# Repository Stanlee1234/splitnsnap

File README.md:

# splitnsnap
A 75% Keyboard, but it is held together in the middle with magnets, making it a regular and split keyboard, whatever you would want.

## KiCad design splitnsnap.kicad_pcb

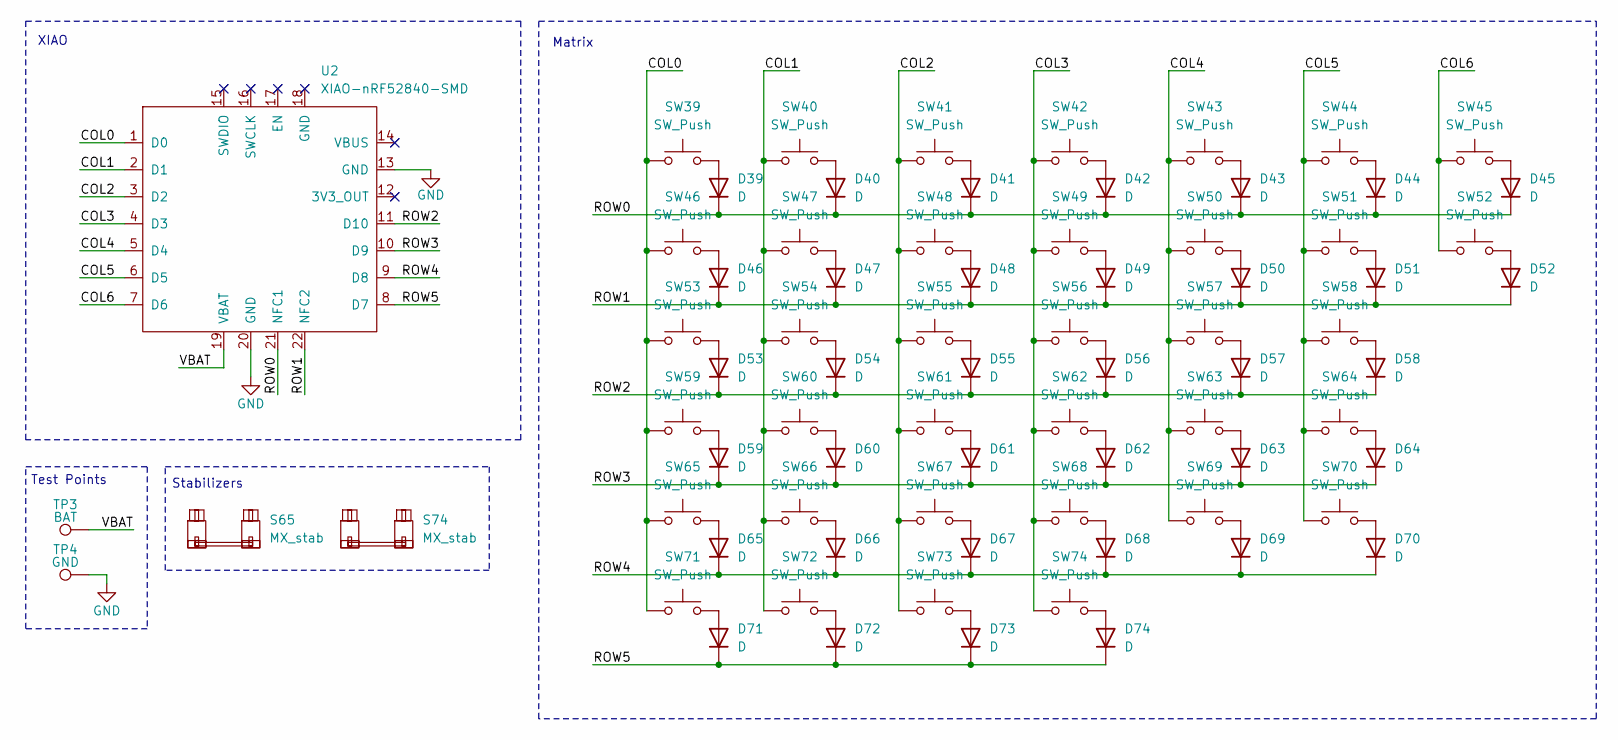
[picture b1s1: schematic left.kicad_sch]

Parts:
D39, D40, D41, D42, D43, D44, D45, D46, D47, D48, D49, D50, D51, D52, D53, D54, D55, D56, D57, D58, D59, D60, D61, D62, D63, D64, D65, D66, D67, D68, D69, D70, D71, D72, D73, D74: D; D_SOD-123
S65: MX_stab; STAB_MX_2.25u
S74: MX_stab; STAB_MX_2.75u
SW39, SW40, SW41, SW42, SW43, SW44, SW45, SW46, SW47, SW48, SW49, SW50, SW51, SW52, SW54, SW55, SW56, SW57, SW58, SW60, SW61, SW62, SW63, SW64, SW66, SW67, SW68, SW69, SW70, SW73: SW_Push; Hotswap_MX_1.00u
SW53: SW_Push; Hotswap_MX_1.50u
SW59: SW_Push; Hotswap_MX_1.75u
SW65: SW_Push; Hotswap_MX_2.25u
SW71, SW72: SW_Push; Hotswap_MX_1.25u
SW74: SW_Push; Hotswap_MX_2.75u
TP3: BAT; TestPoint_Pad_D2.0mm
TP4: GND; TestPoint_Pad_D2.0mm
U2: XIAO-nRF52840-SMD; modified-XIAO-nRF52840-SMD

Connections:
/left/COL0: SW39.1, SW46.1, SW53.1, SW59.1, SW65.1, SW71.1, U2.1 (D0)
/left/COL1: SW40.1, SW47.1, SW54.1, SW60.1, SW66.1, SW72.1, U2.2 (D1)
/left/COL2: SW41.1, SW48.1, SW55.1, SW61.1, SW67.1, SW73.1, U2.3 (D2)
/left/COL3: SW42.1, SW49.1, SW56.1, SW62.1, SW68.1, SW74.1, U2.4 (D3)
/left/COL4: SW43.1, SW50.1, SW57.1, SW63.1, SW69.1, U2.5 (D4)
/left/COL5: SW44.1, SW51.1, SW58.1, SW64.1, SW70.1, U2.6 (D5)
/left/COL6: SW45.1, SW52.1, U2.7 (D6)
/left/ROW0: D39.1 (K), D40.1 (K), D41.1 (K), D42.1 (K), D43.1 (K), D44.1 (K), D45.1 (K), U2.21 (NFC1)
/left/ROW1: D46.1 (K), D47.1 (K), D48.1 (K), D49.1 (K), D50.1 (K), D51.1 (K), D52.1 (K), U2.22 (NFC2)
/left/ROW2: D53.1 (K), D54.1 (K), D55.1 (K), D56.1 (K), D57.1 (K), D58.1 (K), U2.11 (D10)
/left/ROW3: D59.1 (K), D60.1 (K), D61.1 (K), D62.1 (K), D63.1 (K), D64.1 (K), U2.10 (D9)
/left/ROW4: D65.1 (K), D66.1 (K), D67.1 (K), D68.1 (K), D69.1 (K), D70.1 (K), U2.9 (D8)
/left/ROW5: D71.1 (K), D72.1 (K), D73.1 (K), D74.1 (K), U2.8 (D7)
/left/VBAT: TP3.1 (1_1), U2.19 (VBAT)
GND: TP4.1 (1_1), U2.13 (GND), U2.20 (GND); also elsewhere on the board
unnamed: D39.2 (A), SW39.2
unnamed: D40.2 (A), SW40.2
unnamed: D41.2 (A), SW41.2
unnamed: D42.2 (A), SW42.2
unnamed: D43.2 (A), SW43.2
unnamed: D44.2 (A), SW44.2
unnamed: D45.2 (A), SW45.2
unnamed: D46.2 (A), SW46.2
unnamed: D47.2 (A), SW47.2
unnamed: D48.2 (A), SW48.2
unnamed: D49.2 (A), SW49.2
unnamed: D50.2 (A), SW50.2
unnamed: D51.2 (A), SW51.2
unnamed: D52.2 (A), SW52.2
unnamed: D53.2 (A), SW53.2
unnamed: D54.2 (A), SW54.2
unnamed: D55.2 (A), SW55.2
unnamed: D56.2 (A), SW56.2
unnamed: D57.2 (A), SW57.2
unnamed: D58.2 (A), SW58.2
unnamed: D59.2 (A), SW59.2
unnamed: D60.2 (A), SW60.2
unnamed: D61.2 (A), SW61.2
unnamed: D62.2 (A), SW62.2
unnamed: D63.2 (A), SW63.2
unnamed: D64.2 (A), SW64.2
unnamed: D65.2 (A), SW65.2
unnamed: D66.2 (A), SW66.2
unnamed: D67.2 (A), SW67.2
unnamed: D68.2 (A), SW68.2
unnamed: D69.2 (A), SW69.2
unnamed: D70.2 (A), SW70.2
unnamed: D71.2 (A), SW71.2
unnamed: D72.2 (A), SW72.2
unnamed: D73.2 (A), SW73.2
unnamed: D74.2 (A), SW74.2

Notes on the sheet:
Matrix
XIAO
Stabilizers
Test Points

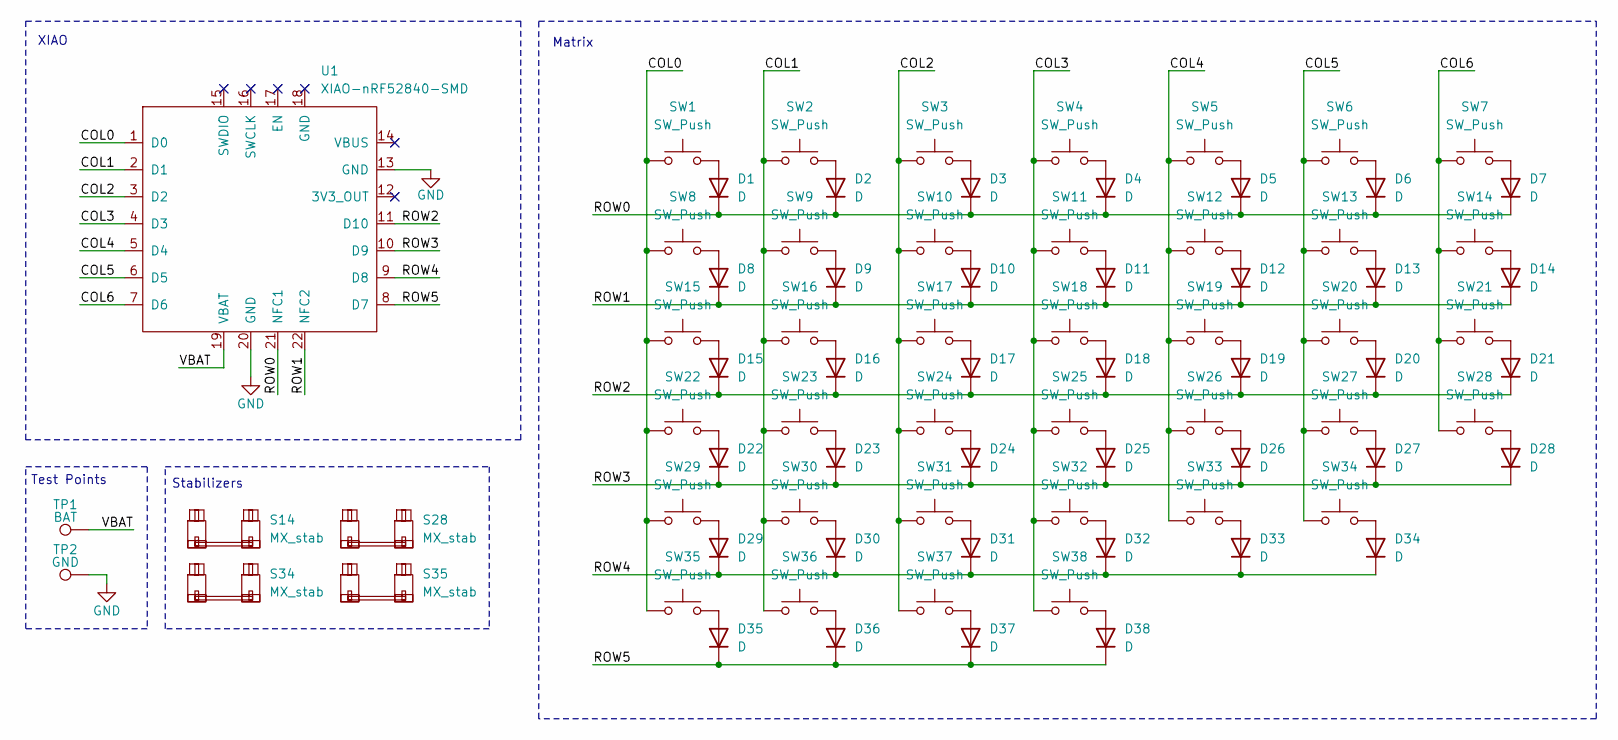
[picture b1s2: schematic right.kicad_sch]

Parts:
D1, D2, D3, D4, D5, D6, D7, D8, D9, D10, D11, D12, D13, D14, D15, D16, D17, D18, D19, D20, D21, D22, D23, D24, D25, D26, D27, D28, D29, D30, D31, D32, D33, D34, D35, D36, D37, D38: D; D_SOD-123
S14: MX_stab; STAB_MX_2u
S28: MX_stab; STAB_MX_2.25u
S34, S35: MX_stab; STAB_MX_2.75u
SW1, SW2, SW3, SW4, SW5, SW6, SW8, SW9, SW10, SW11, SW12, SW13, SW15, SW16, SW17, SW18, SW19, SW20, SW21, SW22, SW23, SW24, SW25, SW26, SW27, SW29, SW30, SW31, SW32, SW33: SW_Push; Hotswap_MX_1.00u
SW7: SW_Push; Hotswap_MX_1.50u
SW14: SW_Push; Hotswap_MX_2.00u
SW28: SW_Push; Hotswap_MX_2.25u
SW34, SW35: SW_Push; Hotswap_MX_2.75u
SW36, SW37, SW38: SW_Push; Hotswap_MX_1.25u
TP1: BAT; TestPoint_Pad_D2.0mm
TP2: GND; TestPoint_Pad_D2.0mm
U1: XIAO-nRF52840-SMD; modified-XIAO-nRF52840-SMD

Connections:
/right/COL0: SW1.1, SW8.1, SW15.1, SW22.1, SW29.1, SW35.1, U1.1 (D0)
/right/COL1: SW2.1, SW9.1, SW16.1, SW23.1, SW30.1, SW36.1, U1.2 (D1)
/right/COL2: SW3.1, SW10.1, SW17.1, SW24.1, SW31.1, SW37.1, U1.3 (D2)
/right/COL3: SW4.1, SW11.1, SW18.1, SW25.1, SW32.1, SW38.1, U1.4 (D3)
/right/COL4: SW5.1, SW12.1, SW19.1, SW26.1, SW33.1, U1.5 (D4)
/right/COL5: SW6.1, SW13.1, SW20.1, SW27.1, SW34.1, U1.6 (D5)
/right/COL6: SW7.1, SW14.1, SW21.1, SW28.1, U1.7 (D6)
/right/ROW0: D1.1 (K), D2.1 (K), D3.1 (K), D4.1 (K), D5.1 (K), D6.1 (K), D7.1 (K), U1.21 (NFC1)
/right/ROW1: D8.1 (K), D9.1 (K), D10.1 (K), D11.1 (K), D12.1 (K), D13.1 (K), D14.1 (K), U1.22 (NFC2)
/right/ROW2: D15.1 (K), D16.1 (K), D17.1 (K), D18.1 (K), D19.1 (K), D20.1 (K), D21.1 (K), U1.11 (D10)
/right/ROW3: D22.1 (K), D23.1 (K), D24.1 (K), D25.1 (K), D26.1 (K), D27.1 (K), D28.1 (K), U1.10 (D9)
/right/ROW4: D29.1 (K), D30.1 (K), D31.1 (K), D32.1 (K), D33.1 (K), D34.1 (K), U1.9 (D8)
/right/ROW5: D35.1 (K), D36.1 (K), D37.1 (K), D38.1 (K), U1.8 (D7)
/right/VBAT: TP1.1 (1_1), U1.19 (VBAT)
GND: TP2.1 (1_1), U1.13 (GND), U1.20 (GND); also elsewhere on the board
unnamed: D1.2 (A), SW1.2
unnamed: D2.2 (A), SW2.2
unnamed: D3.2 (A), SW3.2
unnamed: D4.2 (A), SW4.2
unnamed: D5.2 (A), SW5.2
unnamed: D6.2 (A), SW6.2
unnamed: D7.2 (A), SW7.2
unnamed: D8.2 (A), SW8.2
unnamed: D9.2 (A), SW9.2
unnamed: D10.2 (A), SW10.2
unnamed: D11.2 (A), SW11.2
unnamed: D12.2 (A), SW12.2
unnamed: D13.2 (A), SW13.2
unnamed: D14.2 (A), SW14.2
unnamed: D15.2 (A), SW15.2
unnamed: D16.2 (A), SW16.2
unnamed: D17.2 (A), SW17.2
unnamed: D18.2 (A), SW18.2
unnamed: D19.2 (A), SW19.2
unnamed: D20.2 (A), SW20.2
unnamed: D21.2 (A), SW21.2
unnamed: D22.2 (A), SW22.2
unnamed: D23.2 (A), SW23.2
unnamed: D24.2 (A), SW24.2
unnamed: D25.2 (A), SW25.2
unnamed: D26.2 (A), SW26.2
unnamed: D27.2 (A), SW27.2
unnamed: D28.2 (A), SW28.2
unnamed: D29.2 (A), SW29.2
unnamed: D30.2 (A), SW30.2
unnamed: D31.2 (A), SW31.2
unnamed: D32.2 (A), SW32.2
unnamed: D33.2 (A), SW33.2
unnamed: D34.2 (A), SW34.2
unnamed: D35.2 (A), SW35.2
unnamed: D36.2 (A), SW36.2
unnamed: D37.2 (A), SW37.2
unnamed: D38.2 (A), SW38.2

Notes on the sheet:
Matrix
Test Points
XIAO
Stabilizers

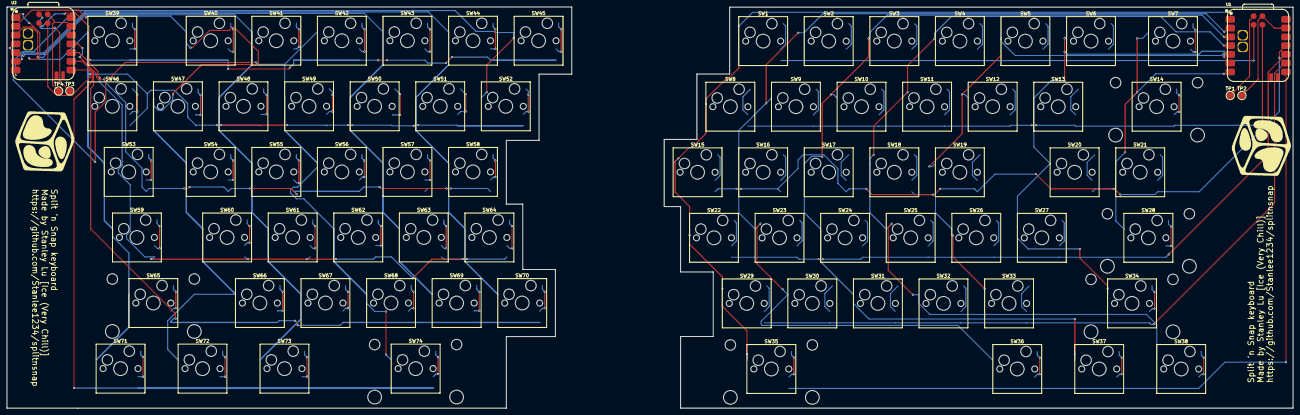
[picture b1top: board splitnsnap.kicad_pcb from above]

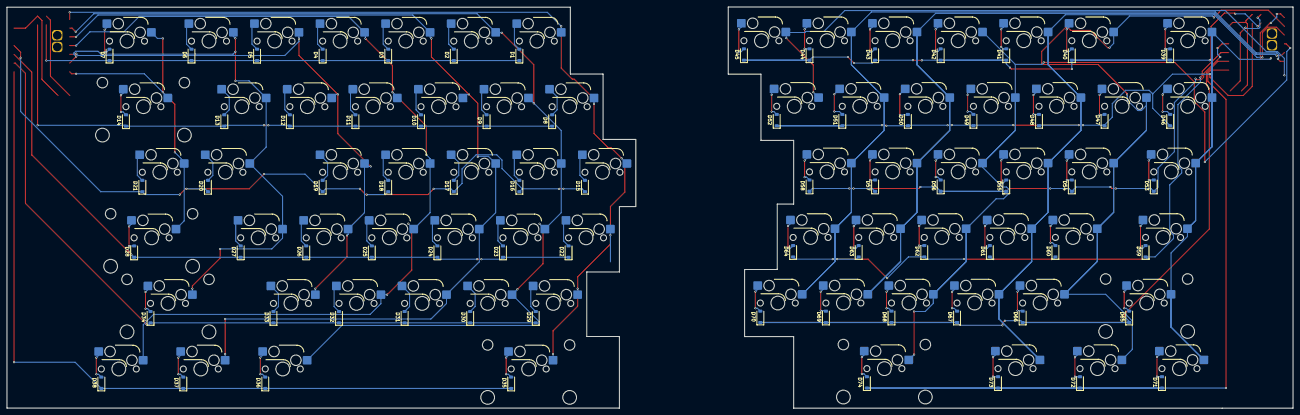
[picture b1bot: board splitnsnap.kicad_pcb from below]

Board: 2 copper layers, 373.6 x 116.5 mm, 160 parts (74 on the bottom side), 103 nets.

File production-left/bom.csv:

Designator,Footprint,Quantity,Value,LCSC Part #
"D39, D40, D41, D42, D43, D44, D45, D46, D47, D48, D49, D50, D51, D52, D53, D54, D55, D56, D57, D58, D59, D60, D61, D62, D63, D64, D65, D66, D67, D68, D69, D70, D71, D72, D73, D74",D_SOD-123,36,D,
S65,STAB_MX_2.25u,1,MX_stab,
S74,STAB_MX_2.75u,1,MX_stab,
"SW39, SW40, SW41, SW42, SW43, SW44, SW45, SW46, SW47, SW48, SW49, SW50, SW51, SW52, SW54, SW55, SW56, SW57, SW58, SW60, SW61, SW62, SW63, SW64, SW66, SW67, SW68, SW69, SW70",Hotswap_MX_1.00u,29,SW_Push,
SW53,Hotswap_MX_1.50u,1,SW_Push,
SW59,Hotswap_MX_1.75u,1,SW_Push,
SW65,Hotswap_MX_2.25u,1,SW_Push,
"SW71, SW72, SW73",Hotswap_MX_1.25u,3,SW_Push,
SW74,Hotswap_MX_2.75u,1,SW_Push,
TP3,TestPoint_Pad_D2.0mm,1,BAT,
TP4,TestPoint_Pad_D2.0mm,1,GND,
U2,modified-XIAO-nRF52840-SMD,1,XIAO-nRF52840-SMD,
